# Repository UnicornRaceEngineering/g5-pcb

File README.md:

g5-pcb
======

pcb designs for the g5 car

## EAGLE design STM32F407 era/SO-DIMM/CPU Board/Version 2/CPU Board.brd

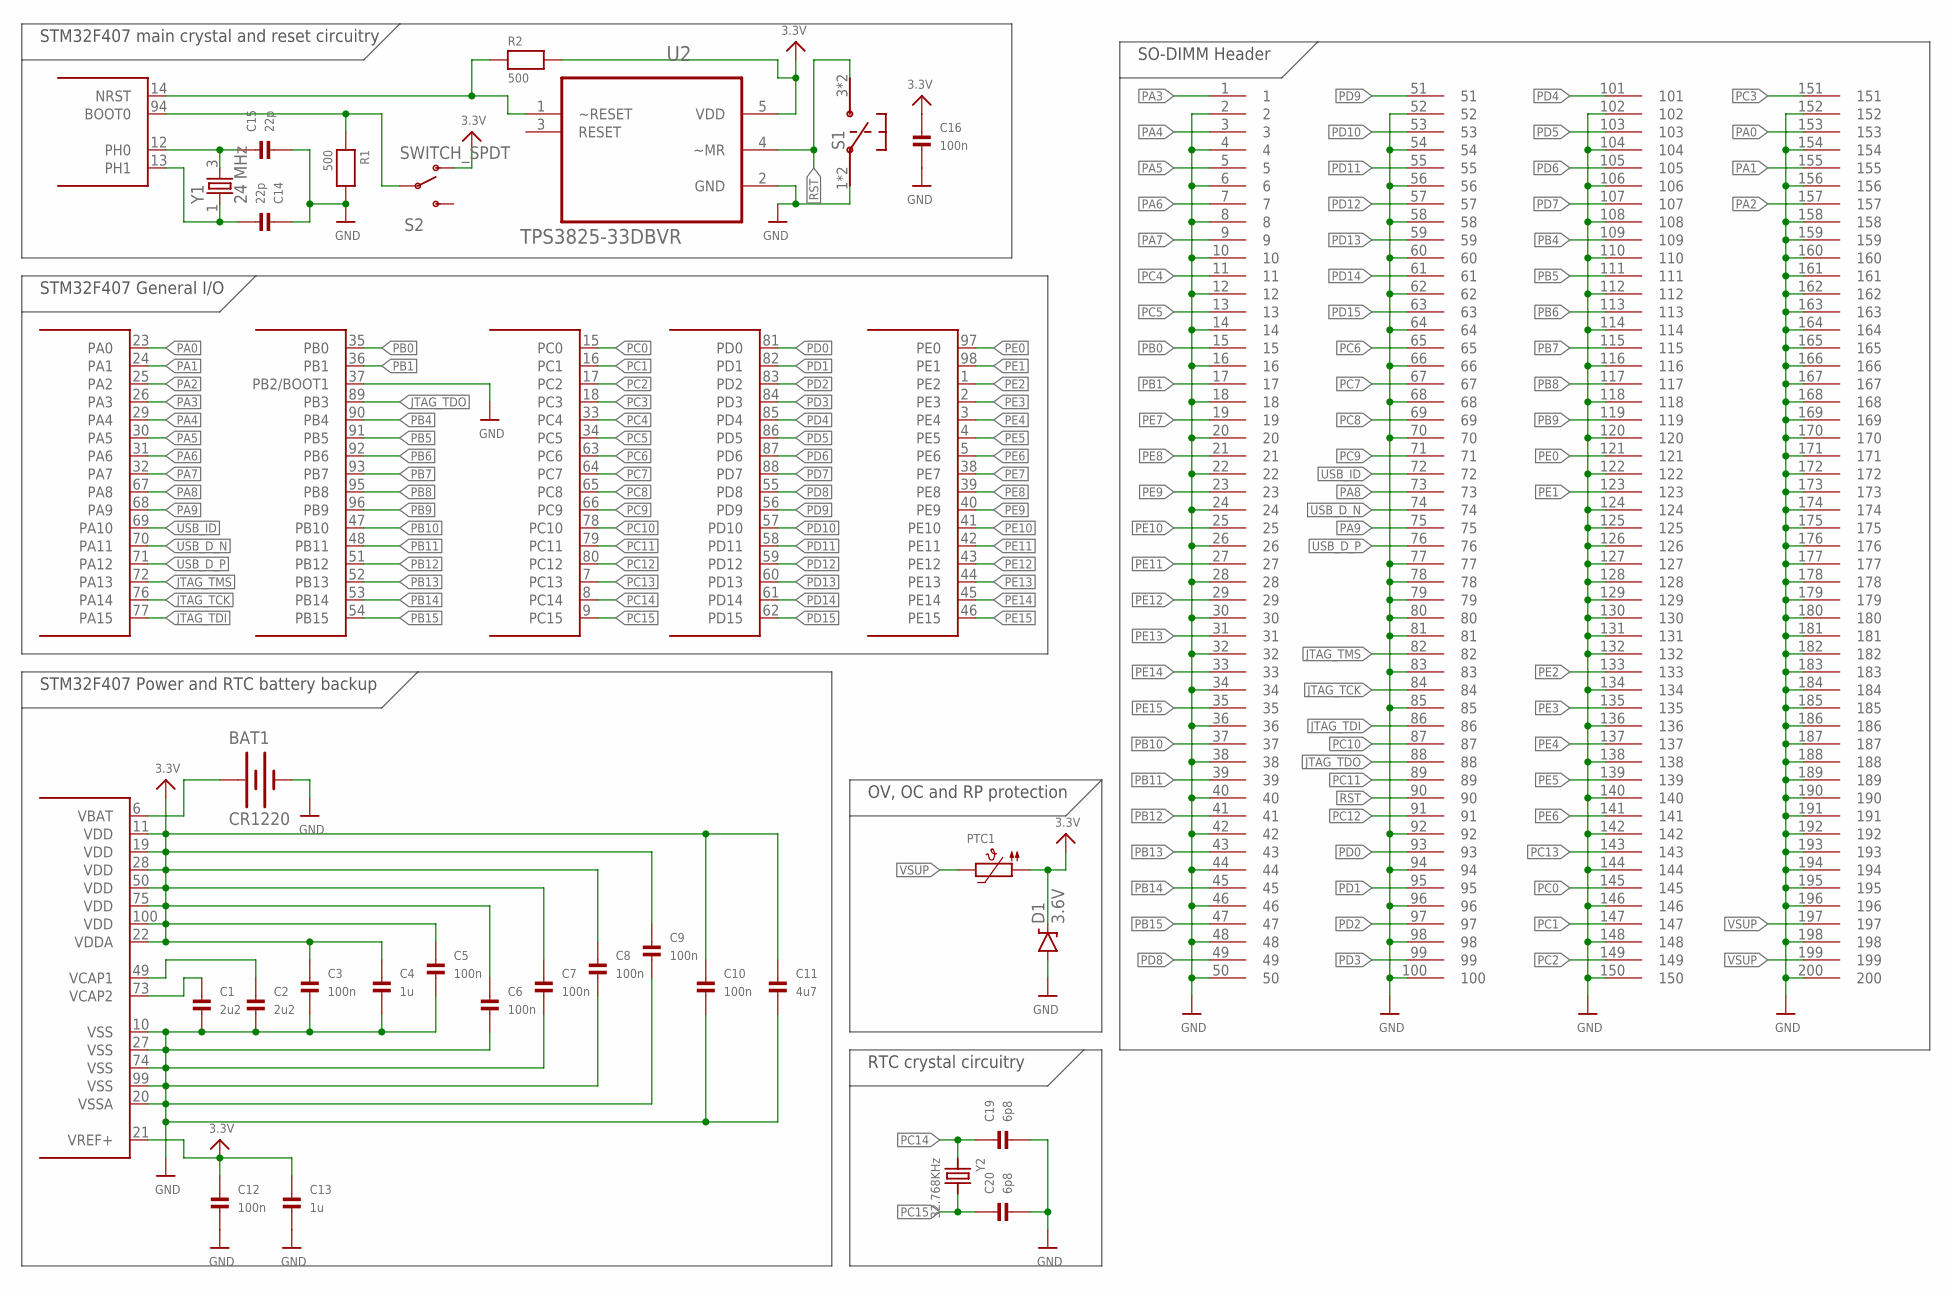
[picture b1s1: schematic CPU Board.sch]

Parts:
BAT1: CR1220; BATTCON_12MM_PTH
C1, C2: 2u2; _0603
C3, C5, C6, C7, C8, C9, C10, C12, C16: 100n; _0603
C4, C13: 1u; _0603
C11: 4u7; _0603
C14, C15: 22p; _0603
C19, C20: 6p8; _0603
D1: 3.6V; SOD-323
PTC1: PTC1206; 1206
R1, R2: 500; _0603
S1: PTS645SM43SMTR92; PTS645
S2: SWITCH_SPDT; KPS-1290
U1: STM32F4-100; SQFP-S-14X14-100
U2: TPS3825-33DBVR; SOT95P280X145-5N
U$19: SODIMM-2.5V-PCB
Y1: 24 MHz; CRYSTAL-4PIN
Y2: 32.768KHz; CRYSTAL_CYL_2X6MM_SMT

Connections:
3.3V: C3.1, C4.1, C5.1, C6.1, C7.1, C8.1, C9.1, C10.1, C11.1, C12.1, C13.1, C16.1, D1.C, PTC1.1, R2.2, S2.O, U1.11 (VDD), U1.19 (VDD), U1.21 (VREF+), U1.22 (VDDA), U1.28 (VDD), U1.50 (VDD), U1.75 (VDD), U1.100 (VDD), U2.5 (VDD)
GND: BAT1.GND (-), C1.2, C2.2, C3.2, C4.2, C5.2, C6.2, C7.2, C8.2, C9.2, C10.2, C11.2, C12.2, C13.2, C14.1, C15.2, C16.2, C19.2, C20.2, D1.A, R1.2, S1.1, S1.2, U1.10 (VSS), U1.20 (VSSA), U1.27 (VSS), U1.37 (PB2/BOOT1), U1.74 (VSS), U1.99 (VSS), U2.2 (GND), U$19.2, U$19.4, U$19.6, U$19.8, U$19.10, U$19.12, U$19.14, U$19.16, U$19.18, U$19.20, U$19.22, U$19.24, U$19.26, U$19.28, U$19.30, U$19.32, U$19.34, U$19.36, U$19.38, U$19.40, U$19.42, U$19.44, U$19.46, U$19.48, U$19.50, U$19.52, U$19.54, U$19.56, U$19.58, U$19.60, U$19.62, U$19.64, U$19.66, U$19.68, U$19.70, U$19.77, U$19.78, U$19.79, U$19.80, U$19.81, U$19.83, U$19.85, U$19.92, U$19.94, U$19.96, U$19.98, U$19.100, U$19.102, U$19.104, U$19.106, U$19.108, U$19.110, U$19.112, U$19.114, U$19.116, U$19.118, U$19.120, U$19.122, U$19.124, U$19.125, U$19.126, U$19.127, U$19.128, U$19.129, U$19.130, U$19.131, U$19.132, U$19.134, U$19.136, U$19.138, U$19.140, U$19.142, U$19.144, U$19.146, U$19.148, U$19.150, U$19.152, U$19.154, U$19.156, U$19.158, U$19.159, U$19.160, U$19.161, U$19.162, U$19.163, U$19.164, U$19.165, U$19.166, U$19.167, U$19.168, U$19.169, U$19.170, U$19.171, U$19.172, U$19.173, U$19.174, U$19.175, U$19.176, U$19.177, U$19.178, U$19.179, U$19.180, U$19.181, U$19.182, U$19.183, U$19.184, U$19.185, U$19.186, U$19.187, U$19.188, U$19.189, U$19.190, U$19.191, U$19.192, U$19.193, U$19.194, U$19.195, U$19.196, U$19.198, U$19.200
JTAG_TCK: U1.76 (PA14), U$19.84
JTAG_TDI: U1.77 (PA15), U$19.86
JTAG_TDO: U1.89 (PB3), U$19.88
JTAG_TMS: U1.72 (PA13), U$19.82
unnamed: C15.1, U1.12 (PH0), Y1.3 (2)
unnamed: C1.1, U1.73 (VCAP2)
unnamed: C2.1, U1.49 (VCAP1)
unnamed: R1.1, S2.P, U1.94 (BOOT0)
unnamed: BAT1.VCC@1 (+), U1.6 (VBAT)
unnamed: C14.2, U1.13 (PH1), Y1.1
PA0: U1.23 (PA0), U$19.153
PA1: U1.24 (PA1), U$19.155
PA2: U1.25 (PA2), U$19.157
PA3: U1.26 (PA3), U$19.1
PA4: U1.29 (PA4), U$19.3
PA5: U1.30 (PA5), U$19.5
PA6: U1.31 (PA6), U$19.7
PA7: U1.32 (PA7), U$19.9
PA8: U1.67 (PA8), U$19.73
PA9: U1.68 (PA9), U$19.75
PB0: U1.35 (PB0), U$19.15
PB1: U1.36 (PB1), U$19.17
PB4: U1.90 (PB4), U$19.109
PB5: U1.91 (PB5), U$19.111
PB6: U1.92 (PB6), U$19.113
PB7: U1.93 (PB7), U$19.115
PB8: U1.95 (PB8), U$19.117
PB9: U1.96 (PB9), U$19.119
PB10: U1.47 (PB10), U$19.37
PB11: U1.48 (PB11), U$19.39
PB12: U1.51 (PB12), U$19.41
PB13: U1.52 (PB13), U$19.43
PB14: U1.53 (PB14), U$19.45
PB15: U1.54 (PB15), U$19.47
PC0: U1.15 (PC0), U$19.145
PC1: U1.16 (PC1), U$19.147
PC2: U1.17 (PC2), U$19.149
PC3: U1.18 (PC3), U$19.151
PC4: U1.33 (PC4), U$19.11
PC5: U1.34 (PC5), U$19.13
PC6: U1.63 (PC6), U$19.65
PC7: U1.64 (PC7), U$19.67
PC8: U1.65 (PC8), U$19.69
PC9: U1.66 (PC9), U$19.71
PC10: U1.78 (PC10), U$19.87
PC11: U1.79 (PC11), U$19.89
PC12: U1.80 (PC12), U$19.91
PC13: U1.7 (PC13), U$19.143
PC14: C19.1, U1.8 (PC14), Y2.1
PC15: C20.1, U1.9 (PC15), Y2.2
PD0: U1.81 (PD0), U$19.93
PD1: U1.82 (PD1), U$19.95
PD2: U1.83 (PD2), U$19.97
PD3: U1.84 (PD3), U$19.99
PD4: U1.85 (PD4), U$19.101
PD5: U1.86 (PD5), U$19.103
PD6: U1.87 (PD6), U$19.105
PD7: U1.88 (PD7), U$19.107
PD8: U1.55 (PD8), U$19.49
PD9: U1.56 (PD9), U$19.51
PD10: U1.57 (PD10), U$19.53
PD11: U1.58 (PD11), U$19.55
PD12: U1.59 (PD12), U$19.57
PD13: U1.60 (PD13), U$19.59
PD14: U1.61 (PD14), U$19.61
PD15: U1.62 (PD15), U$19.63
PE0: U1.97 (PE0), U$19.121
PE1: U1.98 (PE1), U$19.123
PE2: U1.1 (PE2), U$19.133
PE3: U1.2 (PE3), U$19.135
PE4: U1.3 (PE4), U$19.137
PE5: U1.4 (PE5), U$19.139
PE6: U1.5 (PE6), U$19.141
PE7: U1.38 (PE7), U$19.19
PE8: U1.39 (PE8), U$19.21
PE9: U1.40 (PE9), U$19.23
PE10: U1.41 (PE10), U$19.25
PE11: U1.42 (PE11), U$19.27
PE12: U1.43 (PE12), U$19.29
PE13: U1.44 (PE13), U$19.31
PE14: U1.45 (PE14), U$19.33
PE15: U1.46 (PE15), U$19.35
RESET: R2.1, U1.14 (NRST), U2.1 (~RESET)
RST: S1.3, S1.4, U2.4 (~MR), U$19.90
USB_D_N: U1.70 (PA11), U$19.74
USB_D_P: U1.71 (PA12), U$19.76
USB_ID: U1.69 (PA10), U$19.72
VSUP: PTC1.2, U$19.197, U$19.199

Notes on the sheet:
STM32F407 Power and RTC battery backup
STM32F407 main crystal and reset circuitry
RTC crystal circuitry
STM32F407 General I/O
OV, OC and RP protection
SO-DIMM Header

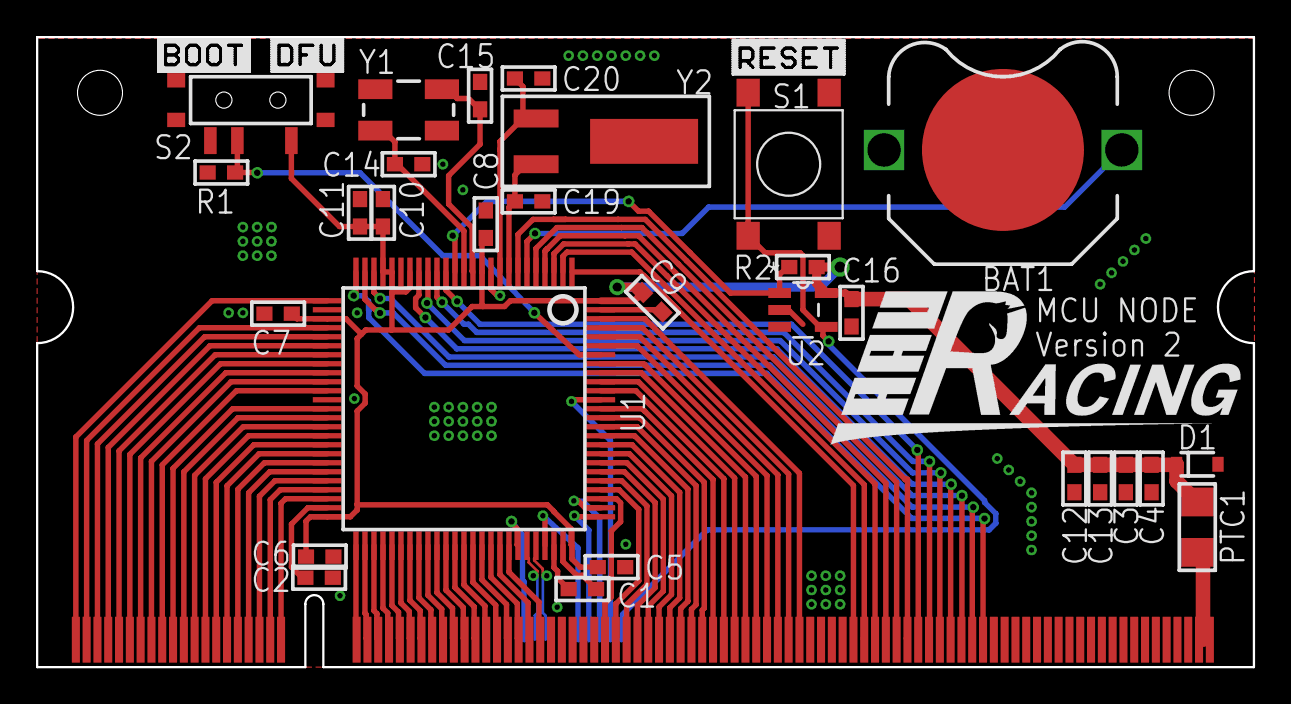
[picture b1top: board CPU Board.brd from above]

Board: 2 copper layers, 67.6 x 35.0 mm, 30 parts (0 on the bottom side), 90 nets.

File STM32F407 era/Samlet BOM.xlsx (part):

COM-TC | CPU | Dash | Debug | Dev | Tele | USB | H-Bridge | Relay
1 | 1 | 1 | 1 | 1 | 1 | 1 | 0 | 1
Qty | Value | Device | Package | Link
6 | CPU standoff |  |  | https://www.digikey.dk/product-detail/en/wurth-electronics-i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
4 | 057-014-1 | 057-014-1 | 057-014-1 | http://dk.farnell.com/amphenol/t821114a1s100ceu/header-verti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
1 |  | 10-XX | B3F-10XX | http://dk.farnell.com/c-k-components/pts645sl43-2-lfs/tactil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
2 | 22-23-2021 | 22-23-2021 | 22-23-2021 | http://dk.farnell.com/molex/22-23-2021/header-pin-2way/dp/1462926
2 | 22-23-2031 | 22-23-2031 | 22-23-2031 | http://dk.farnell.com/molex/22-23-2031/header-pin-3way/dp/14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
0 | 22-23-2071 | 22-23-2071 | 22-23-2071 | http://dk.farnell.com/molex/22-23-2071/pin-header/dp/1654534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
4 | 22-27-2041-04 | 22-27-2041-04 | 6410-04 | http://dk.farnell.com/molex/22-27-2041/header-square-pin-2-5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
1 | 4N33 | 4N33 | DIL06 | http://dk.farnell.com/vishay/4n33/optocoupler-5-3kv-transist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
1 | 5566-6 | 5566-6 | 5566-6 | http://dk.farnell.com/molex/39-29-9063/connector-header-6pos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
4 | 74HC595N | 74HC595N | DIL16 | http://dk.farnell.com/texas-instruments/sn74hc595n/shift-reg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
 | ARDUINOR3-DIMENSION | ARDUINOR3-DIMENSION | ARDUINOR3
6 |  | AUDIO-JACKPTH | AUDIO-JACK | http://dk.farnell.com/cliff-electronic-components/fc68131/st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
2 | CON1 | AUTOCONNECTOR | AUTOCONNECTOR | http://dk.farnell.com/molex/36638-0002/header-cmc-single-por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
1 | AVR_SPI_PRG_6NS | AVR_SPI_PRG_6NS | 2X3-NS | http://dk.farnell.com/multicomp/2214s-06sg-85/connector-rece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
6 | BA340A | B340A | SMA-DIODE | https://dk.rs-online.com/web/p/dioder-ensretter-og-schottky-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
1 | CR1220 | BATTERY12PTH | BATTCON_12MM_PTH | https://dk.rs-online.com/web/p/batteriholdere/2197948/
8 | BN35N61 | BN35N61 | B35N61 | http://dk.farnell.com/greenpar-te-connectivity/1-1478204-0/r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
51 | 100n | CAP_CERAMIC_0603 | _0603 | http://dk.farnell.com/walsin/0603b104k250ct/capacitor-mlcc-x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
4 | 10n | CAP_CERAMIC_0603 | _0603 | http://dk.farnell.com/kemet/c0603c103k5rac7081/cap-mlcc-x7r-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
6 | 1n | CAP_CERAMIC_0603 | _0603 | http://dk.farnell.com/walsin/0603b102k250ct/cap-mlcc-x7r-100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
2 | 1u | CAP_CERAMIC_0603 | _0603 | http://dk.farnell.com/walsin/0603x105k250ct/capacitor-mlcc-x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
5 | 22p | CAP_CERAMIC_0603 | _0603 | http://dk.farnell.com/wurth-elektronik/885012006034/cap-mlcc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
2 | 27p | CAP_CERAMIC_0603 | _0603 | http://dk.farnell.com/walsin/0603n270j500ct/capacitor-mlcc-n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
2 | 2u2 | CAP_CERAMIC_0603 | _0603 | http://dk.farnell.com/murata/grm188r61e225ka12d/cap-mlcc-x5r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
4 | 47n | CAP_CERAMIC_0603 | _0603 | http://dk.farnell.com/walsin/0603b473k250ct/capacitor-mlcc-x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
3 | 47p | CAP_CERAMIC_0603 | _0603 | http://dk.farnell.com/multicomp/mcmt18n470f250ct/cap-mlcc-c0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
1 | 4u7 | CAP_CERAMIC_0603 | _0603 | http://dk.farnell.com/murata/grt188r61e475ke13d/cap-mlcc-aut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
2 | 6p8 | CAP_CERAMIC_0603 | _0603 | http://dk.farnell.com/multicomp/mcmt18n6r8c250ct/cap-mlcc-c0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
2 | 10u | CAP_CERAMIC_0805 | _0805 | http://dk.farnell.com/murata/grm21br61e106ma73l/cap-mlcc-x5r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
1 | 1u | CAP_CERAMIC_0805 | _0805 | http://dk.farnell.com/murata/grm219f51e105za01d/cap-mlcc-y5v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
1 | 220n50V | CAP_CERAMIC_0805 | _0805 | http://dk.farnell.com/walsin/0805f224z500ct/capacitor-mlcc-y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
6 | 22u | CAP_CERAMIC_0805 | _0805 | http://dk.farnell.com/murata/grm21br61c226me44l/cap-mlcc-x5r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
2 | 2u | CAP_CERAMIC_0805 | _0805 | http://dk.farnell.com/murata/grm21br71e225ke11l/cap-mlcc-x7r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
6 | 4,7u | CAP_CERAMIC_0805 | _0805 | http://dk.farnell.com/murata/grm21br61e475ma12l/cap-mlcc-x5r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
4 | 47u | CAP_CERAMIC_0805 | _0805 | http://dk.farnell.com/tdk/c2012x5r1a476m125ac/cap-mlcc-x5r-4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
2 | 100u 6v3 | CAP_CERAMIC1206 | 1206 | http://dk.farnell.com/murata/grm31cf50j107ze01l/cap-mlcc-y5v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
1 | 150u 6v3 | CAP_CERAMIC1206 | 1206 | http://dk.farnell.com/murata/grm31cr60j157me11l/capacitor-ml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
0 | 2000u | CPOL-EUE10-22.5 | EB22,5D | http://dk.farnell.com/multicomp/mcksk035m222m25s/capacitor-a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
1 | 32.768KHz | CRYSTAL32.768 | CRYSTAL_CYL_2X6MM_SMT | http://dk.farnell.com/iqd-frequency-products/lfxtal002997/cr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
1 | 24 MHz | CRYSTAL4PIN | CRYSTAL-4PIN | http://dk.farnell.com/qantek-technology-corporation/qc5a24-0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
3 | 12MHz | CRYSTALHC49S | HC49/S | http://dk.farnell.com/iqd-frequency-products/lfxtal003215/cr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
2 | 6MHz | CRYSTALHC49S | HC49/S | http://dk.farnell.com/qantek-technology-corporation/qcl6-000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
2 |  | DB9FEMALE | DB9 | http://dk.farnell.com/multicomp/5504f1-09s-02a-03/receptacle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
3 |  | DCBARRELPTH | DCJACK_2MM_PTH | http://dk.farnell.com/multicomp/mj-180ph/socket-pcb-dc-power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
5 |  | DIODESMA | SMADIODE | http://dk.farnell.com/bourns/cd1607-b140lf/diode-schottky-1a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
6 |  | DIODESOD-323F | SOD-323F | http://dk.farnell.com/nexperia/pmeg6010cej/schottky-rectifie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
1 | 3.6V | DIODE-ZENER3.3V | SOD-323 | http://dk.farnell.com/nexperia/pdz3-3b-115/diode-zener-0-4w-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
1 | EA-DOGXL160W-7 | EA-DOGXL160W-7 | EA-DOGXL160W-7 | https://dk.rs-online.com/web/p/lcd-monokrome-displays/7588765/
1 | EA-DOGXL160W-7 BL |  |  | https://www.digikey.dk/products/en?keywords=EA-LED78x64-W
1 |  | EG1218S | EG1218 | http://dk.farnell.com/e-switch/eg1218/slide-switch-spdt-0-2a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
1 | EM406 | EM406 | EM406 | http://dk.farnell.com/jst-japan-solderless-terminals/bm06b-s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
1 | CAT4238TD-GT3 | FAN5331 | SOT23-5 | https://dk.rs-online.com/web/p/lysdiode-led-driver-icer/7893859/
4 | FTDI_DEVICE | FTDI_DEVICE | FTDI_DEVICE_SIDE | http://dk.farnell.com/multicomp/mc34751/connector-header-tht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
4 | FUSE_SOCKET | FUSE_SOCKET | FUSE_SOCKET_12V_30A | http://dk.farnell.com/te-connectivity/vcf4-1000/socket-relay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
1 | GTL2000 | GTL2000 | TSSOP48 | http://dk.farnell.com/nxp/gtl2000dgg-112/volt-level-translat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
1 | SRN6045TA-220M | INDUCTORTDK_VLC6045 | INDUCTOR_6X6MM_TDK_VLC6045 | http://dk.farnell.com/bourns/srn6045ta-220m/inductor-aec-q20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
2 | SRN6045TA-680M | INDUCTORTDK_VLC6045 | INDUCTOR_6X6MM_TDK_VLC6045 | http://dk.farnell.com/bourns/srn6045ta-680m/inductor-aec-q20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
2 | IRF9332PBF | IRF9332PBF | SOIC127P600X175-8N | http://dk.farnell.com/infineon/irf9332pbf/mosfet-p-ch-diode-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
1 |  | JST_4PIN | JSTPH4 | http://dk.farnell.com/jst-japan-solderless-terminals/s4b-ph-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
3 | JTAG-ARM | JTAG-ARM | JTAG-ARM | http://dk.farnell.com/amphenol/t821120a1s100ceu/header-verti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
30 |  | LED_RGB_PLCC4 | RGBLED_PLCC4 | http://dk.farnell.com/broadcom-limited/asmb-mtb1-0a3a2/led-h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
20 |  | LED1206 | CHIPLED_1206 | https://www.digikey.dk/product-detail/en/qt-brightek-qtb/QBL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
6 |  | LEDCHIPLED_0805 | CHIPLED_0805 | https://www.digikey.dk/product-detail/en/lumex-opto-componen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
4 | LITTE_FUSE | LITTE_FUSE | LITTE_FUSE_PAC | http://dk.farnell.com/littelfuse/01530008z/fuseholder-mini-p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
4 | 3,3V | LM1117SOT223-REFLOW | SOT223-R | http://dk.farnell.com/stmicroelectronics/ld1117s33tr/v-reg-l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
3 | 5V | LM1117SOT223-REFLOW | SOT223-R | http://dk.farnell.com/stmicroelectronics/ld1117s50ctr/ic-v-r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
3 | LoPy | LOPY | LOPY | https://dk.rs-online.com/web/p/hojfrekvens-udviklingssaet/1368855/
1 | LSM6DS3 | LSM6DS3DOT_INDICATION | LGA14L_DOT_INDICATOR | http://dk.farnell.com/stmicroelectronics/lsm6ds3htr/mems-mod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
1 | MAX232AEWE+ | MAX232AEWE+ | SOIC127P1032X265-16N | http://dk.farnell.com/maxim-integrated-products/max232aewe-t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
1 | MAX608ESA+ | MAX608ESA+ | SO08 | http://dk.farnell.com/maxim-integrated-products/max608esa/dc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
2 | MAX6818 | MAX6818 | SOP20 | http://dk.farnell.com/maxim-integrated-products/max6818eap-t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
2 | MAX9926 | MAX9926 | SOP63P600X175-16N | https://dk.rs-online.com/web/p/hall-effekt-sensor-icer/9237731/
1 | MBR0520LT | MBR0520LT | SOD123 | http://dk.farnell.com/on-semiconductor/mbr0520lt1g/diode-sch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
3 | MCP2200 | MCP2200 | SO20L | http://dk.farnell.com/microchip/mcp2200-i-so/ic-usb2-0-to-ua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
4 | MCP6004-E/SL | MCP6004-E/SL | SOIC127P600X175-14N | http://dk.farnell.com/microchip/mcp6004-e-sl/ic-op-amp-quad-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
2 | MICROFIT4 | MICROFIT4 | 43045-0400 | https://dk.rs-online.com/web/p/printstiftlister/2332955/
2 | MICROSD | MICROSD | MICROSD | http://dk.farnell.com/molex/503398-0891/connector-micro-sd-p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

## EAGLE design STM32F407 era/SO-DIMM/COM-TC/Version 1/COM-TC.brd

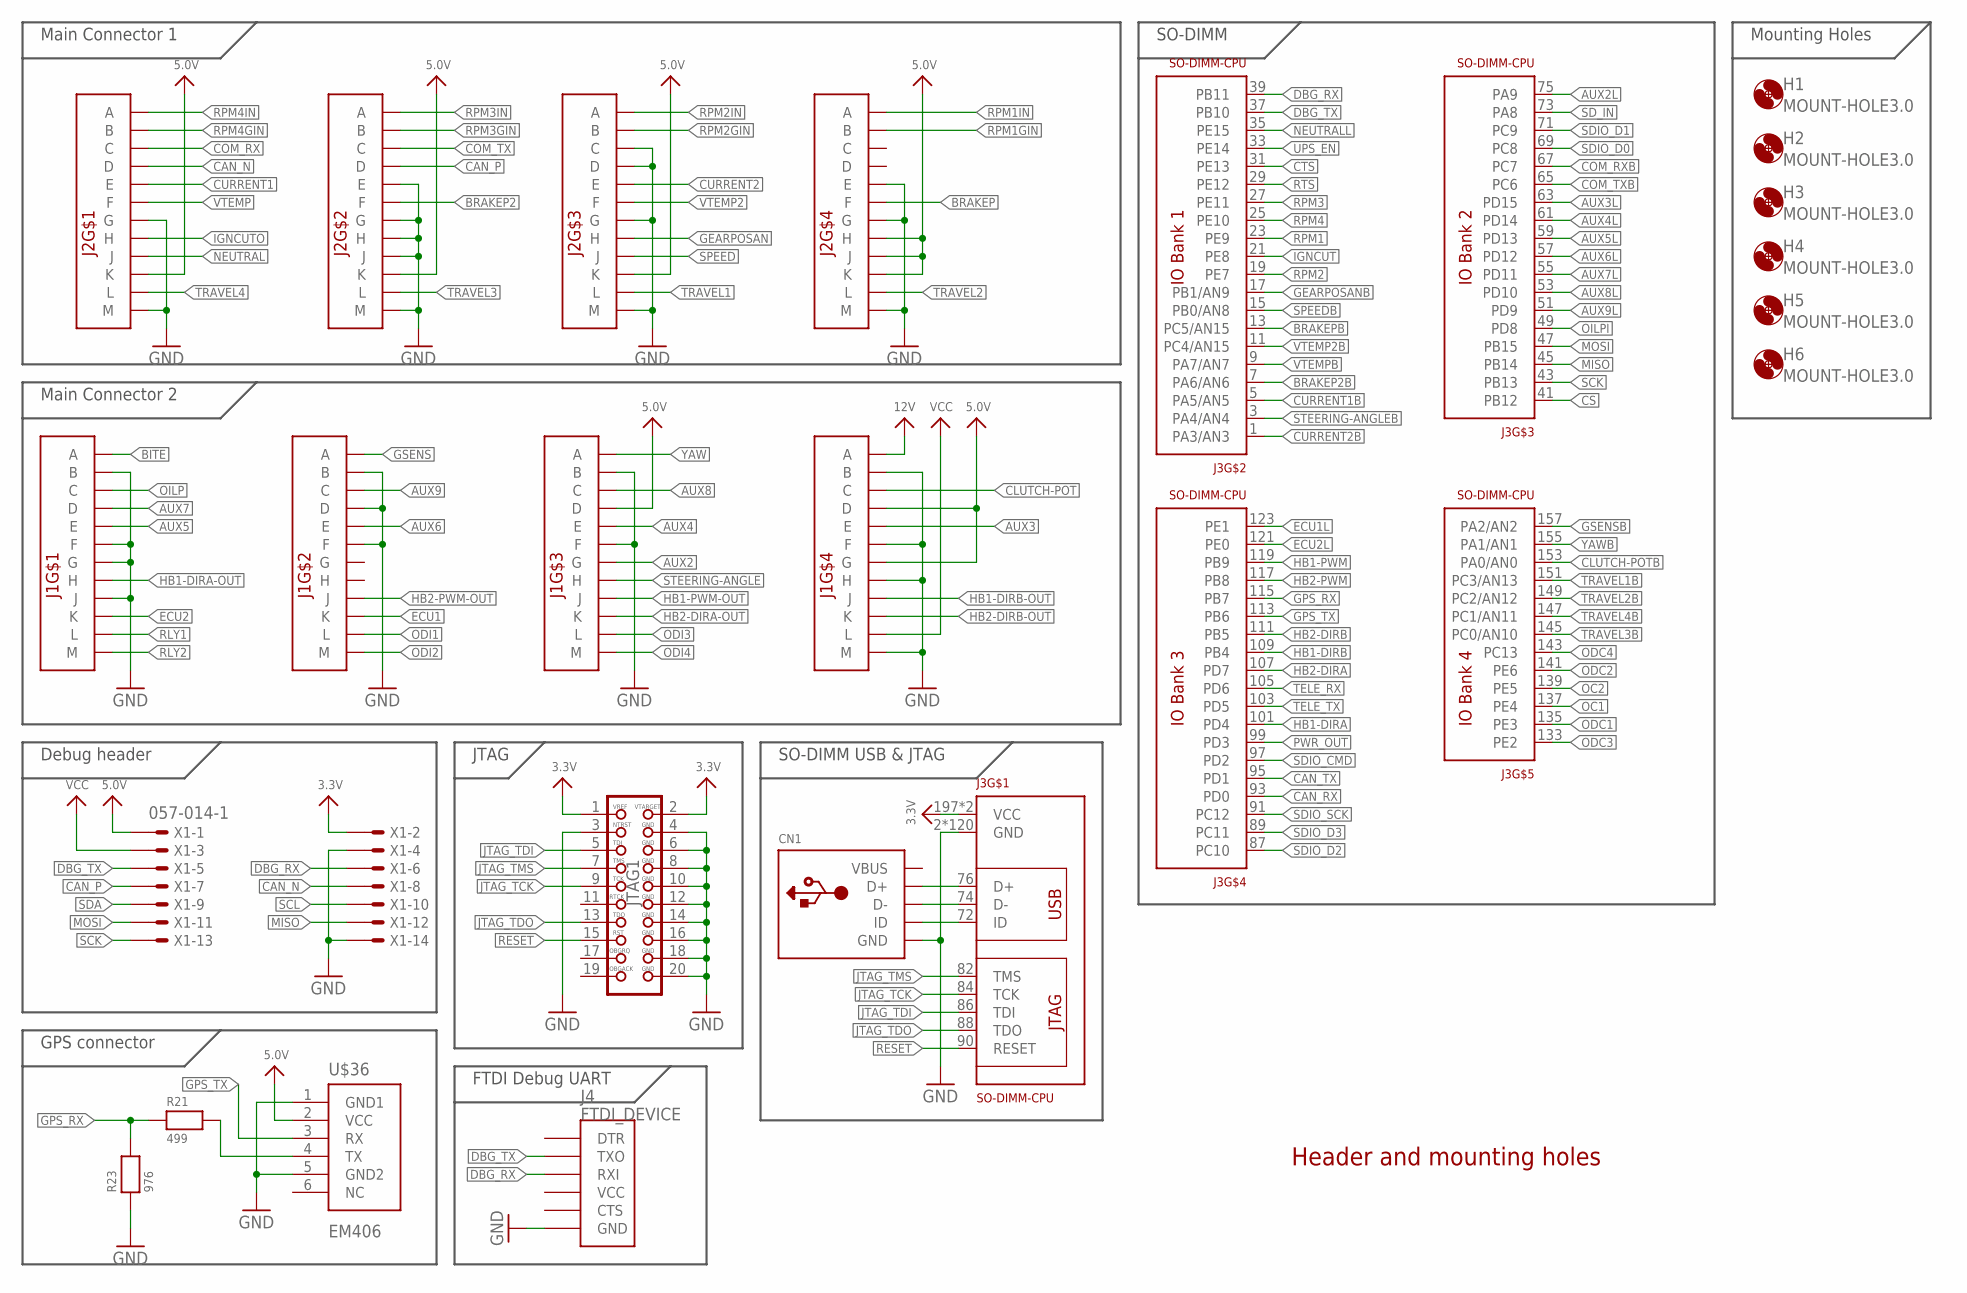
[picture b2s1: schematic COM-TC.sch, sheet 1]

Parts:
CN1: USBMINIBLARGE; USB-MINIB_LARGER
H1, H2, H3, H4, H5, H6: MOUNT-HOLE3.0; 3,0
J1, J2: CON1; AUTOCONNECTOR
J3: SO-DIMM-CPU; SODIMM-CONNECTOR-2.5V
J4: FTDI_DEVICE; FTDI_DEVICE_SIDE
JTAG1: JTAG-ARM
R21: 499; _0603
R23: 976; _0603
U$36: EM406
X1: 057-014-1

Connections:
3.3V: J3.197 (VCC), J3.199 (VCC), JTAG1.1, JTAG1.2, X1.2; also elsewhere on the board
5.0V: J1.D3 (D), J1.D4 (D), J1.G4 (G), J2.H4 (H), J2.J4 (J), J2.K1 (K), J2.K2 (K), J2.K3 (K), J2.K4 (K), U$36.2 (VCC), X1.1; also elsewhere on the board
12V: J1.A4 (A); also elsewhere on the board
AUX2: J1.G3 (G); also elsewhere on the board
AUX2L: J3.75 (PA9); also elsewhere on the board
AUX3: J1.E4 (E); also elsewhere on the board
AUX3L: J3.63 (PD15); also elsewhere on the board
AUX4: J1.E3 (E); also elsewhere on the board
AUX4L: J3.61 (PD14); also elsewhere on the board
AUX5: J1.E1 (E); also elsewhere on the board
AUX5L: J3.59 (PD13); also elsewhere on the board
AUX6: J1.E2 (E); also elsewhere on the board
AUX6L: J3.57 (PD12); also elsewhere on the board
AUX7: J1.D1 (D); also elsewhere on the board
AUX7L: J3.55 (PD11); also elsewhere on the board
AUX8: J1.C3 (C); also elsewhere on the board
AUX8L: J3.53 (PD10); also elsewhere on the board
AUX9: J1.C2 (C); also elsewhere on the board
AUX9L: J3.51 (PD9); also elsewhere on the board
BITE: J1.A1 (A)
BRAKEP: J2.F4 (F); also elsewhere on the board
BRAKEP2: J2.F2 (F); also elsewhere on the board
BRAKEP2B: J3.7 (PA6/AN6); also elsewhere on the board
BRAKEPB: J3.13 (PC5/AN15); also elsewhere on the board
CAN_N: J2.D1 (D), X1.8; also elsewhere on the board
CAN_P: J2.D2 (D), X1.7; also elsewhere on the board
CAN_RX: J3.93 (PD0); also elsewhere on the board
CAN_TX: J3.95 (PD1); also elsewhere on the board
CLUTCH-POT: J1.C4 (C); also elsewhere on the board
CLUTCH-POTB: J3.153 (PA0/AN0); also elsewhere on the board
COM_RX: J2.C1 (C); also elsewhere on the board
COM_RXB: J3.67 (PC7); also elsewhere on the board
COM_TX: J2.C2 (C); also elsewhere on the board
COM_TXB: J3.65 (PC6); also elsewhere on the board
CS: J3.41 (PB12); also elsewhere on the board
CTS: J3.31 (PE13); also elsewhere on the board
CURRENT1: J2.E1 (E); also elsewhere on the board
CURRENT1B: J3.5 (PA5/AN5); also elsewhere on the board
CURRENT2: J2.E3 (E); also elsewhere on the board
CURRENT2B: J3.1 (PA3/AN3); also elsewhere on the board
DBG_RX: J3.39 (PB11), J4.P$3 (RXI), X1.6
DBG_TX: J3.37 (PB10), J4.P$2 (TXO), X1.5
ECU1: J1.K2 (K); also elsewhere on the board
ECU1L: J3.123 (PE1); also elsewhere on the board
ECU2: J1.K1 (K); also elsewhere on the board
ECU2L: J3.121 (PE0); also elsewhere on the board
GEARPOSAN: J2.H3 (H); also elsewhere on the board
GEARPOSANB: J3.17 (PB1/AN9); also elsewhere on the board
GND: CN1.GND, J1.B1 (B), J1.B2 (B), J1.B3 (B), J1.B4 (B), J1.D2 (D), J1.F1 (F), J1.F2 (F), J1.F3 (F), J1.F4 (F), J1.G1 (G), J1.H4 (H), J1.J1 (J), J1.M4 (M), J2.C3 (C), J2.D3 (D), J2.E2 (E), J2.E4 (E), J2.G1 (G), J2.G2 (G), J2.G3 (G), J2.G4 (G), J2.H2 (H), J2.J2 (J), J2.M1 (M), J2.M2 (M), J2.M3 (M), J2.M4 (M), J3.2 (GND), J3.4 (GND), J3.6 (GND), J3.8 (GND), J3.10 (GND), J3.12 (GND), J3.14 (GND), J3.16 (GND), J3.18 (GND), J3.20 (GND), J3.22 (GND), J3.24 (GND), J3.26 (GND), J3.28 (GND), J3.30 (GND), J3.32 (GND), J3.34 (GND), J3.36 (GND), J3.38 (GND), J3.40 (GND), J3.42 (GND), J3.44 (GND), J3.46 (GND), J3.48 (GND), J3.50 (GND), J3.52 (GND), J3.54 (GND), J3.56 (GND), J3.58 (GND), J3.60 (GND), J3.62 (GND), J3.64 (GND), J3.66 (GND), J3.68 (GND), J3.70 (GND), J3.77 (GND), J3.78 (GND), J3.79 (GND), J3.80 (GND), J3.81 (GND), J3.83 (GND), J3.85 (GND), J3.92 (GND), J3.94 (GND), J3.96 (GND), J3.98 (GND), J3.100 (GND), J3.102 (GND), J3.104 (GND), J3.106 (GND), J3.108 (GND), J3.110 (GND), J3.112 (GND), J3.114 (GND), J3.116 (GND), J3.118 (GND), J3.120 (GND), J3.122 (GND), J3.124 (GND), J3.125 (GND), J3.126 (GND), J3.127 (GND), J3.128 (GND), J3.129 (GND), J3.130 (GND), J3.131 (GND), J3.132 (GND), J3.134 (GND), J3.136 (GND), J3.138 (GND), J3.140 (GND), J3.142 (GND), J3.144 (GND), J3.146 (GND), J3.148 (GND), J3.150 (GND), J3.152 (GND), J3.154 (GND), J3.156 (GND), J3.158 (GND), J3.159 (GND), J3.160 (GND), J3.161 (GND), J3.162 (GND), J3.163 (GND), J3.164 (GND), J3.165 (GND), J3.166 (GND), J3.167 (GND), J3.168 (GND), J3.169 (GND), J3.170 (GND), J3.171 (GND), J3.172 (GND), J3.173 (GND), J3.174 (GND), J3.175 (GND), J3.176 (GND), J3.177 (GND), J3.178 (GND), J3.179 (GND), J3.180 (GND), J3.181 (GND), J3.182 (GND), J3.183 (GND), J3.184 (GND), J3.185 (GND), J3.186 (GND), J3.187 (GND), J3.188 (GND), J3.189 (GND), J3.190 (GND), J3.191 (GND), J3.192 (GND), J3.193 (GND), J3.194 (GND), J3.195 (GND), J3.196 (GND), J3.198 (GND), J3.200 (GND), J4.P$6 (GND), JTAG1.3, JTAG1.4, JTAG1.6, JTAG1.8, JTAG1.10, JTAG1.12, JTAG1.14, JTAG1.16, JTAG1.18, JTAG1.20, R23.1, U$36.1 (GND1), U$36.5 (GND2), X1.4, X1.14; also elsewhere on the board
GPS_RX: J3.115 (PB7), R21.1, R23.2
GPS_TX: J3.113 (PB6), U$36.3 (RX)
GSENS: J1.A2 (A); also elsewhere on the board
GSENSB: J3.157 (PA2/AN2); also elsewhere on the board
HB1-DIRA: J3.101 (PD4); also elsewhere on the board
HB1-DIRA-OUT: J1.H1 (H); also elsewhere on the board
HB1-DIRB: J3.109 (PB4); also elsewhere on the board
HB1-DIRB-OUT: J1.J4 (J); also elsewhere on the board
HB1-PWM: J3.119 (PB9); also elsewhere on the board
HB1-PWM-OUT: J1.J3 (J); also elsewhere on the board
HB2-DIRA: J3.107 (PD7); also elsewhere on the board
HB2-DIRA-OUT: J1.K3 (K); also elsewhere on the board
HB2-DIRB: J3.111 (PB5); also elsewhere on the board
HB2-DIRB-OUT: J1.K4 (K); also elsewhere on the board
HB2-PWM: J3.117 (PB8); also elsewhere on the board
HB2-PWM-OUT: J1.J2 (J); also elsewhere on the board
IGNCUT: J3.21 (PE8); also elsewhere on the board
IGNCUTO: J2.H1 (H); also elsewhere on the board
JTAG_TCK: J3.84 (TCK), JTAG1.9
JTAG_TDI: J3.86 (TDI), JTAG1.5
JTAG_TDO: J3.88 (TDO), JTAG1.13
JTAG_TMS: J3.82 (TMS), JTAG1.7
MISO: J3.45 (PB14), X1.12; also elsewhere on the board
MOSI: J3.47 (PB15), X1.11; also elsewhere on the board
unnamed: CN1.ID, J3.72 (ID)
NEUTRAL: J2.J1 (J); also elsewhere on the board
NEUTRALL: J3.35 (PE15); also elsewhere on the board
OC1: J3.137 (PE4); also elsewhere on the board
OC2: J3.139 (PE5); also elsewhere on the board
ODC1: J3.135 (PE3); also elsewhere on the board
ODC2: J3.141 (PE6); also elsewhere on the board
ODC3: J3.133 (PE2); also elsewhere on the board
ODC4: J3.143 (PC13); also elsewhere on the board
ODI1: J1.L2 (L); also elsewhere on the board
ODI2: J1.M2 (M); also elsewhere on the board
ODI3: J1.L3 (L); also elsewhere on the board
ODI4: J1.M3 (M); also elsewhere on the board
OILP: J1.C1 (C); also elsewhere on the board
OILPI: J3.49 (PD8); also elsewhere on the board
PWR_OUT: J3.99 (PD3); also elsewhere on the board
RESET: J3.90 (RESET), JTAG1.15
RLY1: J1.L1 (L); also elsewhere on the board
RLY2: J1.M1 (M); also elsewhere on the board
RPM1: J3.23 (PE9); also elsewhere on the board
RPM1GIN: J2.B4 (B); also elsewhere on the board
RPM1IN: J2.A4 (A); also elsewhere on the board
RPM2: J3.19 (PE7); also elsewhere on the board
RPM2GIN: J2.B3 (B); also elsewhere on the board
RPM2IN: J2.A3 (A); also elsewhere on the board
RPM3: J3.27 (PE11); also elsewhere on the board
RPM3GIN: J2.B2 (B); also elsewhere on the board
RPM3IN: J2.A2 (A); also elsewhere on the board
RPM4: J3.25 (PE10); also elsewhere on the board
RPM4GIN: J2.B1 (B); also elsewhere on the board
RPM4IN: J2.A1 (A); also elsewhere on the board
RTS: J3.29 (PE12); also elsewhere on the board
RXD1: R21.2, U$36.4 (TX)
SCK: J3.43 (PB13), X1.13; also elsewhere on the board
SCL: X1.10
SDA: X1.9
SDIO_CMD: J3.97 (PD2); also elsewhere on the board
SDIO_D0: J3.69 (PC8); also elsewhere on the board
SDIO_D1: J3.71 (PC9); also elsewhere on the board
SDIO_D2: J3.87 (PC10); also elsewhere on the board
SDIO_D3: J3.89 (PC11); also elsewhere on the board
SDIO_SCK: J3.91 (PC12); also elsewhere on the board
SD_IN: J3.73 (PA8); also elsewhere on the board
SPEED: J2.J3 (J); also elsewhere on the board
SPEEDB: J3.15 (PB0/AN8); also elsewhere on the board
STEERING-ANGLE: J1.H3 (H); also elsewhere on the board
STEERING-ANGLEB: J3.3 (PA4/AN4); also elsewhere on the board
TELE_RX: J3.105 (PD6); also elsewhere on the board
TELE_TX: J3.103 (PD5); also elsewhere on the board
TRAVEL1: J2.L3 (L); also elsewhere on the board
TRAVEL1B: J3.151 (PC3/AN13); also elsewhere on the board
TRAVEL2: J2.L4 (L); also elsewhere on the board
TRAVEL2B: J3.149 (PC2/AN12); also elsewhere on the board
TRAVEL3: J2.L2 (L); also elsewhere on the board
TRAVEL3B: J3.145 (PC0/AN10); also elsewhere on the board
TRAVEL4: J2.L1 (L); also elsewhere on the board
TRAVEL4B: J3.147 (PC1/AN11); also elsewhere on the board
UPS_EN: J3.33 (PE14); also elsewhere on the board
VBUS: CN1.VBUS
VCC: J1.L4 (L), X1.3; also elsewhere on the board
VTEMP: J2.F1 (F); also elsewhere on the board
VTEMP2: J2.F3 (F); also elsewhere on the board
VTEMP2B: J3.11 (PC4/AN15); also elsewhere on the board
VTEMPB: J3.9 (PA7/AN7); also elsewhere on the board
YAW: J1.A3 (A); also elsewhere on the board
YAWB: J3.155 (PA1/AN1); also elsewhere on the board
_N: CN1.D-, J3.74 (D-)
_P: CN1.D+, J3.76 (D+)

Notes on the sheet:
Mounting Holes
Main Connector 1
Main Connector 2
Header and mounting holes
JTAG
FTDI Debug UART
Debug header
GPS connector
SO-DIMM
SO-DIMM USB & JTAG

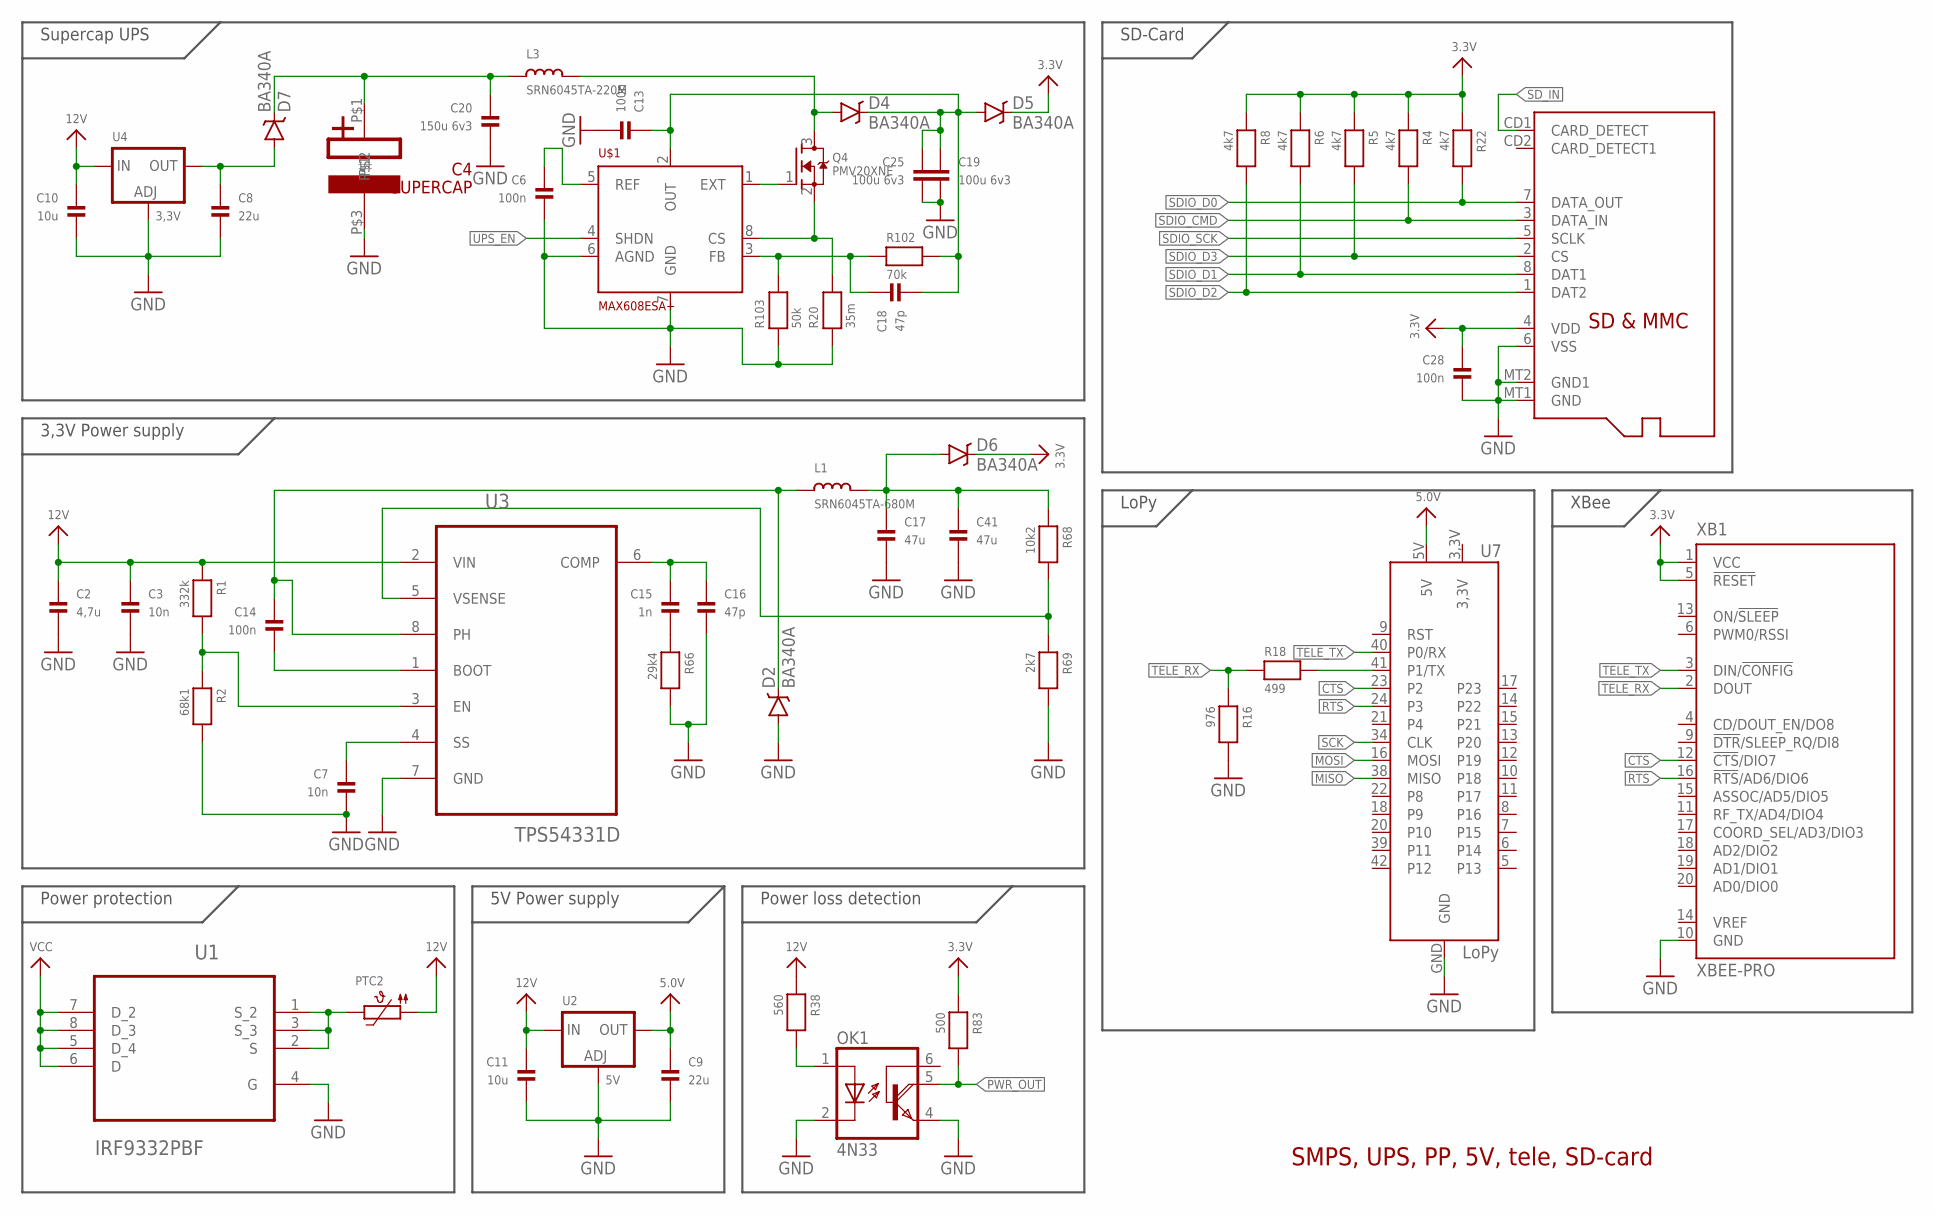
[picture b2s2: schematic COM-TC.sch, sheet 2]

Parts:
C2: 4,7u; _0805
C3, C7: 10n; _0603
C4: SUPERCAP
C6, C13, C14, C28: 100n; _0603
C8, C9: 22u; _0805
C10, C11: 10u; _0805
C15: 1n; _0603
C16, C18: 47p; _0603
C17, C41: 47u; _0805
C19, C25: 100u 6v3; 1206
C20: 150u 6v3; 1206
D2, D4, D5, D6, D7: BA340A; SMA-DIODE
L1: SRN6045TA-680M; INDUCTOR_6X6MM_TDK_VLC6045
L3: SRN6045TA-220M; INDUCTOR_6X6MM_TDK_VLC6045
OK1: 4N33; DIL06
PTC2: PTC1812
Q4: PMV20XNE; SOT23
R1: 332k; _0603
R2: 68k1; _0603
R4, R5, R6, R8, R22: 4k7; _0603
R16: 976; _0603
R18: 499; _0603
R20: 35m; 1206
R38: 560; _0603
R66: 29k4; _0603
R68: 10k2; _0603
R69: 2k7; _0603
R83: 500; _0603
R102: 70k; _0603
R103: 50k; _0603
U1: IRF9332PBF; SOIC127P600X175-8N
U2: 5V; SOT223-R
U3: TPS54331D; SOIC127P600X175-8N
U4: 3,3V; SOT223-R
U7: LoPy; LOPY
U$1: MAX608ESA+; SO08
U$2: MICROSD
XB1: XBEE-PRO

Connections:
3.3V: C28.1, D5.C, D6.C, R4.1, R5.1, R6.1, R8.1, R22.1, R83.1, U$2.4 (VDD), XB1.1 (VCC), XB1.5 (!RESET); also elsewhere on the board
5.0V: C9.1, U2.2 (OUT), U7.5V; also elsewhere on the board
12V: C2.1, C3.1, C10.1, C11.1, PTC2.P$1 (1), R1.1, R38.1, U2.3 (IN), U3.2 (VIN), U4.3 (IN); also elsewhere on the board
CTS: U7.23 (P2), XB1.12 (!CTS!/DIO7); also elsewhere on the board
GND: C2.2, C3.2, C4.P$3, C6.2, C7.2, C8.2, C9.2, C10.2, C11.2, C13.2, C16.2, C17.2, C19.2, C20.2, C25.2, C28.2, C41.2, D2.A, OK1.2 (C), OK1.4 (E), R2.2, R16.2, R20.1, R66.2, R69.2, R103.1, U1.4 (G), U2.1 (ADJ), U3.7 (GND), U4.1 (ADJ), U7.GND, U$1.6 (AGND), U$1.7 (GND), U$2.6 (VSS), U$2.MT1 (GND), U$2.MT2 (GND1), XB1.10 (GND); also elsewhere on the board
MISO: U7.38 (MISO); also elsewhere on the board
MOSI: U7.16 (MOSI); also elsewhere on the board
unnamed: C7.1, U3.4 (SS)
unnamed: R1.2, R2.1, U3.3 (EN)
unnamed: C17.1, C41.1, D6.A, L1.P$2 (2), R68.1
unnamed: C8.1, D7.A, U4.2 (OUT)
unnamed: Q4.1 (G), U$1.1 (EXT)
unnamed: PTC2.P$2 (2), U1.1 (S_2), U1.2 (S), U1.3 (S_3)
unnamed: OK1.1 (A), R38.2
unnamed: Q4.2 (S), R20.2, U$1.8 (CS)
unnamed: C13.1, C18.2, C19.1, C25.1, D4.C, D5.A, R102.2, U$1.2 (OUT)
unnamed: C6.1, U$1.5 (REF)
unnamed: C18.1, R102.1, R103.2, U$1.3 (FB)
unnamed: R18.2, U7.41 (P1/TX)
unnamed: D4.A, L3.P$2 (2), Q4.3 (D)
unnamed: C14.2, U3.1 (BOOT)
unnamed: C14.1, D2.C, L1.P$1 (1), U3.8 (PH)
unnamed: C15.2, R66.1
unnamed: C15.1, C16.1, U3.6 (COMP)
unnamed: R68.2, R69.1, U3.5 (VSENSE)
PWR_OUT: OK1.5 (COL), R83.2; also elsewhere on the board
RTS: U7.24 (P3), XB1.16 (!RTS!/AD6/DIO6); also elsewhere on the board
SCK: U7.34 (CLK); also elsewhere on the board
SDIO_CMD: R4.2, U$2.3 (DATA_IN); also elsewhere on the board
SDIO_D0: R22.2, U$2.7 (DATA_OUT); also elsewhere on the board
SDIO_D1: R6.2, U$2.8 (DAT1); also elsewhere on the board
SDIO_D2: R8.2, U$2.1 (DAT2); also elsewhere on the board
SDIO_D3: R5.2, U$2.2 (CS); also elsewhere on the board
SDIO_SCK: U$2.5 (SCLK); also elsewhere on the board
SD_IN: U$2.CD1 (CARD_DETECT); also elsewhere on the board
SUPERCAP: C4.P$1, C20.1, D7.C, L3.P$1 (1)
TELE_RX: R16.1, R18.1, XB1.2 (DOUT); also elsewhere on the board
TELE_TX: U7.40 (P0/RX), XB1.3 (DIN/!CONFIG); also elsewhere on the board
UPS_EN: U$1.4 (SHDN); also elsewhere on the board
VCC: U1.5 (D_4), U1.6 (D), U1.7 (D_2), U1.8 (D_3); also elsewhere on the board

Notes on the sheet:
Power protection
SD-Card
3,3V Power supply
5V Power supply
Supercap UPS
Power loss detection
XBee
LoPy
SMPS, UPS, PP, 5V, tele, SD-card

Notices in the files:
parts and their libraries:
microbuilder: This work is placed in the public domain, and may be freely used for commercial and non-commercial work with the following conditions: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
SparkFun-DiscreteSemi: Licensing: Creative Commons ShareAlike 4.0 International - https://creativecommons.org/licenses/by-sa/4.0
